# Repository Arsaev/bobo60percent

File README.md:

# bobo60percent
It is a custom mechanical keyboard that I working on.

Features
- clickable knob 
- small screen 
- HHKB like layout 
- rgb highlight and backlight
- USB-C

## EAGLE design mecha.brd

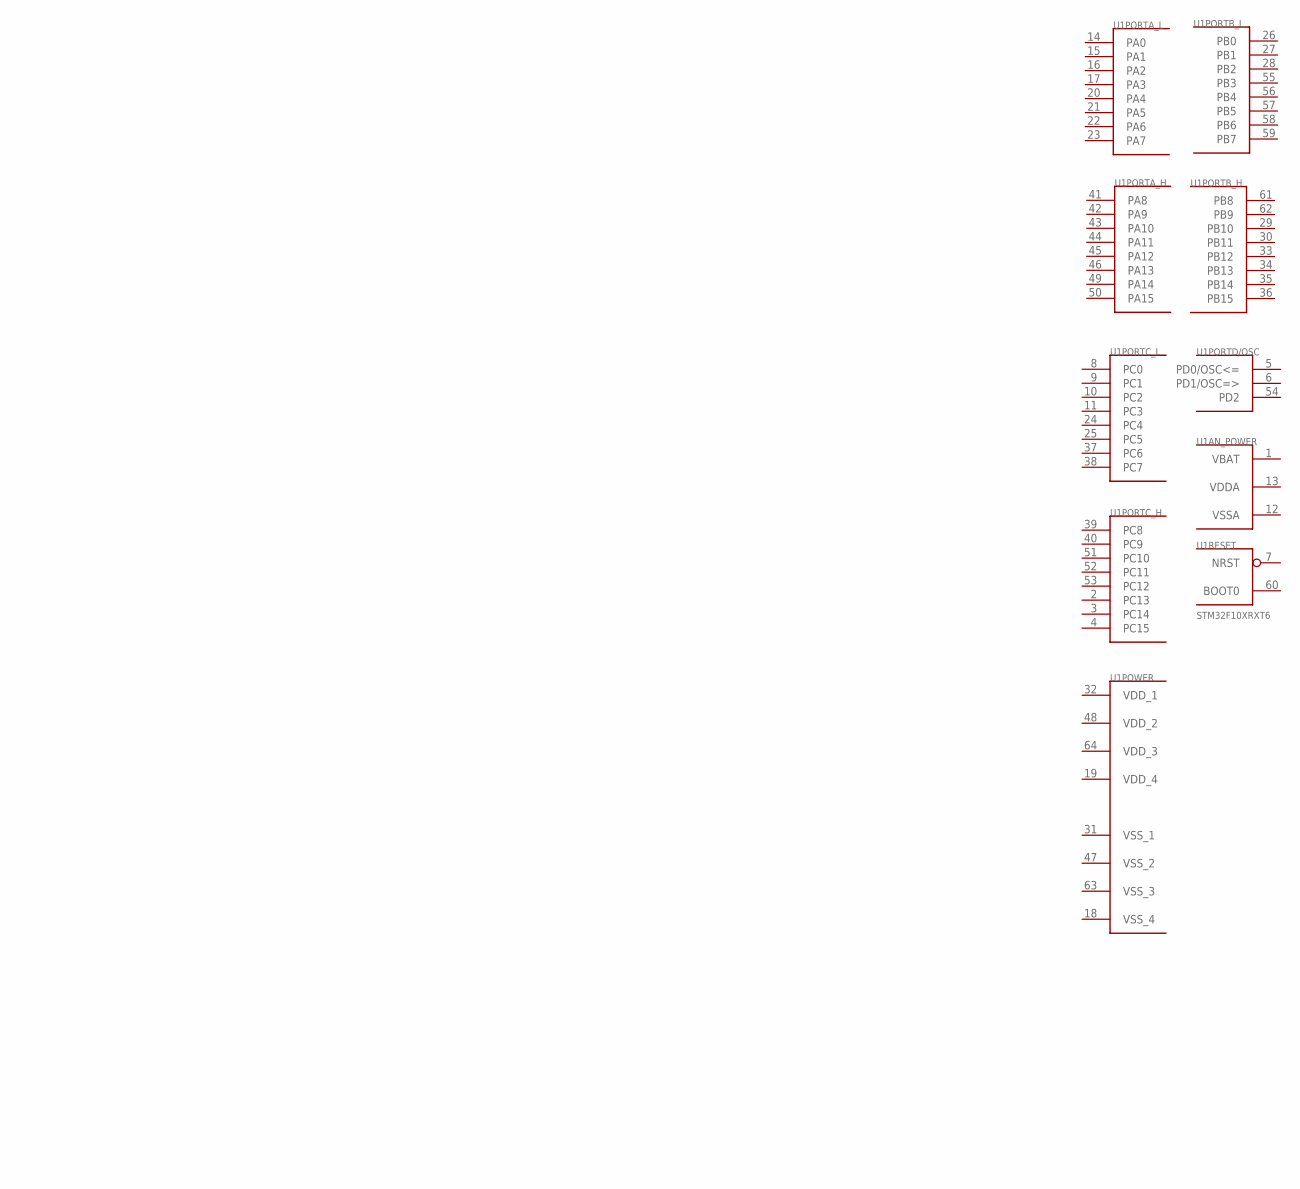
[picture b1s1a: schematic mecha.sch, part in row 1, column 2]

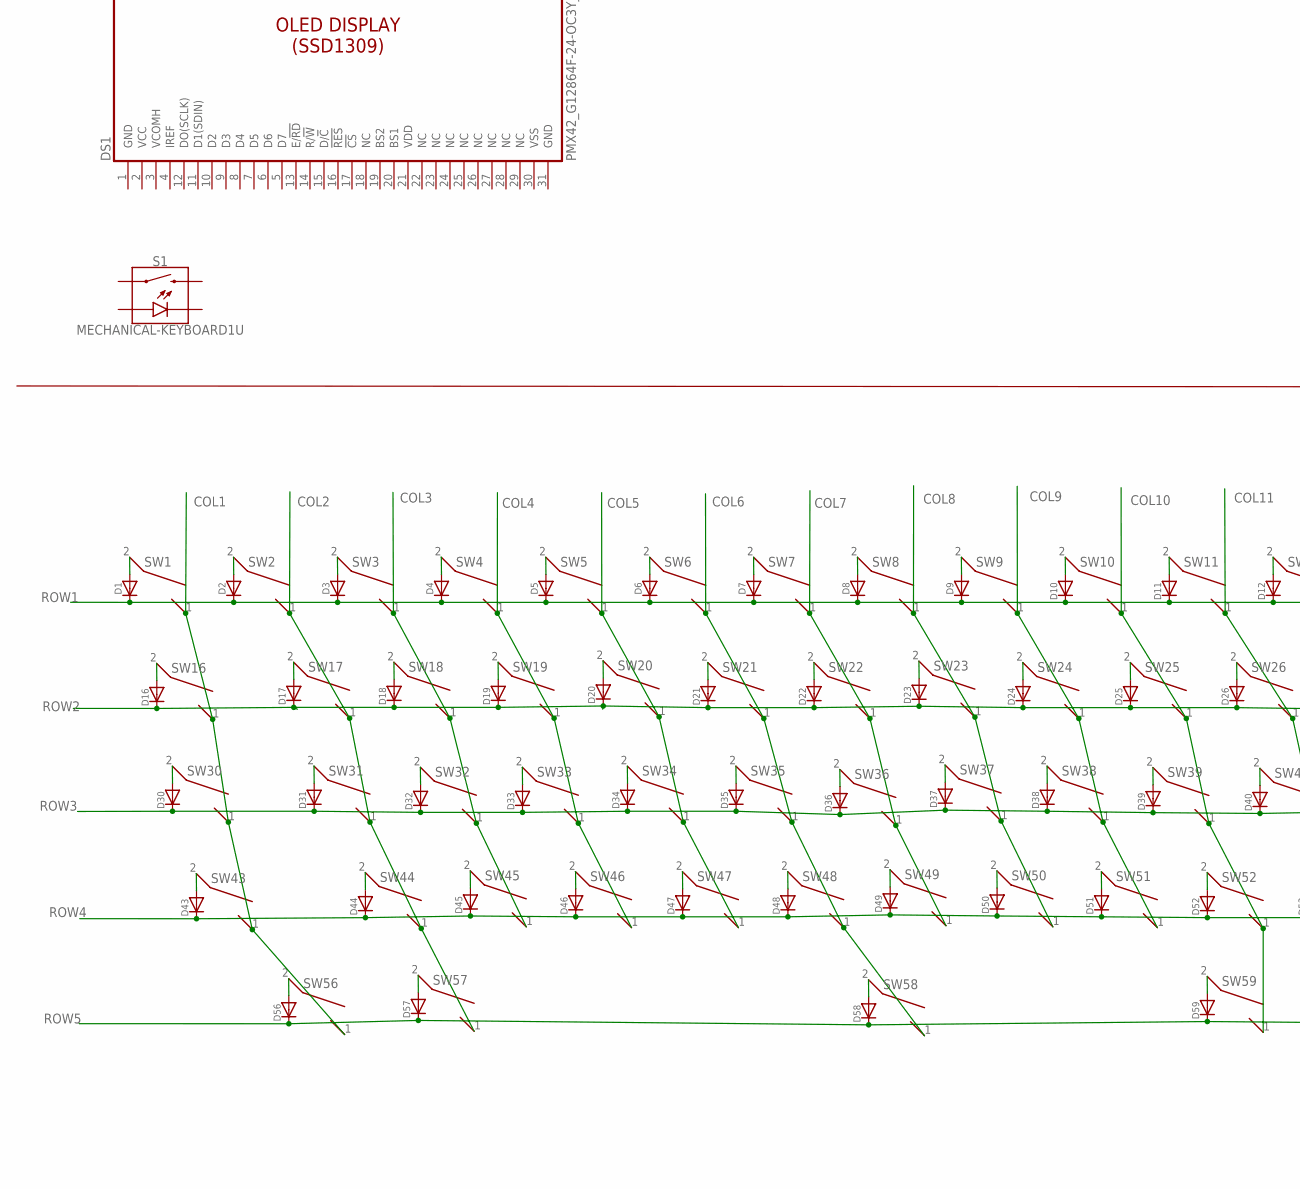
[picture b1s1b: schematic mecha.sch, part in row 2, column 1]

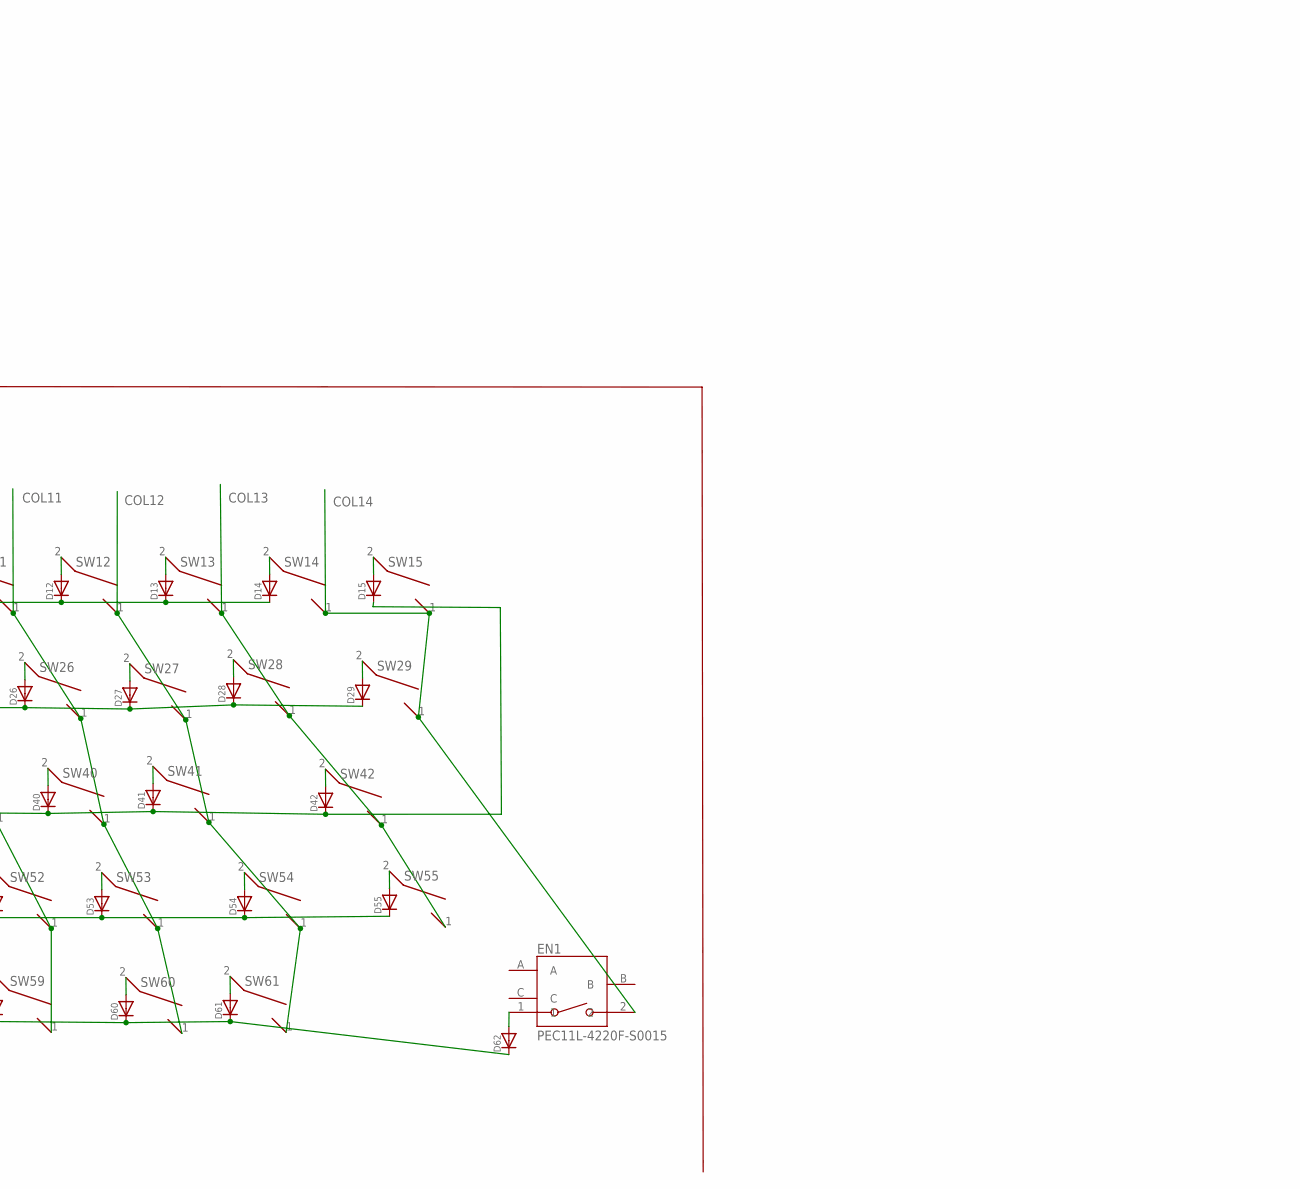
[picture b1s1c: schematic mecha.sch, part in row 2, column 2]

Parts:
D1, D2, D3, D4, D5, D6, D7, D8, D9, D10, D11, D12, D13, D14, D15, D16, D17, D18, D19, D20, D21, D22, D23, D24, D25, D26, D27, D28, D29, D30, D31, D32, D33, D34, D35, D36, D37, D38, D39, D40, D41, D42, D43, D44, D45, D46, D47, D48, D49, D50, D51, D52, D53, D54, D55, D56, D57, D58, D59, D60, D61, D62: DIODESOD-323F; SOD-323F
DS1: PMX42_G12864F-24-OC3Y_BOT
EN1: PEC11L-4220F-S0015
S1: MECHANICAL-KEYBOARD1U; CHERRY-MX-LED-1U
SW1, SW2, SW3, SW4, SW5, SW6, SW7, SW8, SW9, SW10, SW11, SW12, SW13, SW14, SW15, SW16, SW17, SW18, SW19, SW20, SW21, SW22, SW23, SW24, SW25, SW26, SW27, SW28, SW29, SW30, SW31, SW32, SW33, SW34, SW35, SW36, SW37, SW38, SW39, SW40, SW41, SW42, SW43, SW44, SW45, SW46, SW47, SW48, SW49, SW50, SW51, SW52, SW53, SW54, SW55, SW56, SW57, SW58, SW59, SW60, SW61: KAILH_SWITCH_SOCKET; SWITCH_SOCKET
U1: STM32F10XRXT6; TQFP64

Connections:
COL1: SW1.1 (2), SW16.1 (2), SW30.1 (2), SW43.1 (2), SW56.1 (2)
COL2: SW2.1 (2), SW17.1 (2), SW31.1 (2), SW44.1 (2), SW57.1 (2)
COL3: SW3.1 (2), SW18.1 (2), SW32.1 (2), SW45.1 (2)
COL4: SW4.1 (2), SW19.1 (2), SW33.1 (2), SW46.1 (2)
COL5: SW5.1 (2), SW20.1 (2), SW34.1 (2), SW47.1 (2)
COL6: SW6.1 (2), SW21.1 (2), SW35.1 (2), SW48.1 (2), SW58.1 (2)
COL7: SW7.1 (2), SW22.1 (2), SW36.1 (2), SW49.1 (2)
COL8: SW8.1 (2), SW23.1 (2), SW37.1 (2), SW50.1 (2)
COL9: SW9.1 (2), SW24.1 (2), SW38.1 (2), SW51.1 (2)
COL10: SW10.1 (2), SW25.1 (2), SW39.1 (2), SW52.1 (2), SW59.1 (2)
COL11: SW11.1 (2), SW26.1 (2), SW40.1 (2), SW53.1 (2), SW60.1 (2)
COL12: SW12.1 (2), SW27.1 (2), SW41.1 (2), SW54.1 (2), SW61.1 (2)
COL13: SW13.1 (2), SW28.1 (2), SW42.1 (2), SW55.1 (2)
COL14: EN1.2, SW14.1 (2), SW15.1 (2), SW29.1 (2)
GND: DS1.1 (GND), DS1.31 (GND)
unnamed: D1.A, SW1.2 (1)
unnamed: D2.A, SW2.2 (1)
unnamed: D3.A, SW3.2 (1)
unnamed: D4.A, SW4.2 (1)
unnamed: D5.A, SW5.2 (1)
unnamed: D6.A, SW6.2 (1)
unnamed: D7.A, SW7.2 (1)
unnamed: D8.A, SW8.2 (1)
unnamed: D9.A, SW9.2 (1)
unnamed: D10.A, SW10.2 (1)
unnamed: D11.A, SW11.2 (1)
unnamed: D12.A, SW12.2 (1)
unnamed: D13.A, SW13.2 (1)
unnamed: D14.A, SW14.2 (1)
unnamed: D15.A, SW15.2 (1)
unnamed: D16.A, SW16.2 (1)
unnamed: D17.A, SW17.2 (1)
unnamed: D18.A, SW18.2 (1)
unnamed: D19.A, SW19.2 (1)
unnamed: D20.A, SW20.2 (1)
unnamed: D21.A, SW21.2 (1)
unnamed: D22.A, SW22.2 (1)
unnamed: D23.A, SW23.2 (1)
unnamed: D24.A, SW24.2 (1)
unnamed: D25.A, SW25.2 (1)
unnamed: D26.A, SW26.2 (1)
unnamed: D27.A, SW27.2 (1)
unnamed: D28.A, SW28.2 (1)
unnamed: D29.A, SW29.2 (1)
unnamed: D30.A, SW30.2 (1)
unnamed: D31.A, SW31.2 (1)
unnamed: D32.A, SW32.2 (1)
unnamed: D33.A, SW33.2 (1)
unnamed: D34.A, SW34.2 (1)
unnamed: D35.A, SW35.2 (1)
unnamed: D36.A, SW36.2 (1)
unnamed: D37.A, SW37.2 (1)
unnamed: D38.A, SW38.2 (1)
unnamed: D39.A, SW39.2 (1)
unnamed: D40.A, SW40.2 (1)
unnamed: D41.A, SW41.2 (1)
unnamed: D42.A, SW42.2 (1)
unnamed: D43.A, SW43.2 (1)
unnamed: D44.A, SW44.2 (1)
unnamed: D45.A, SW45.2 (1)
unnamed: D46.A, SW46.2 (1)
unnamed: D47.A, SW47.2 (1)
unnamed: D48.A, SW48.2 (1)
unnamed: D49.A, SW49.2 (1)
unnamed: D50.A, SW50.2 (1)
unnamed: D51.A, SW51.2 (1)
unnamed: D52.A, SW52.2 (1)
unnamed: D53.A, SW53.2 (1)
unnamed: D54.A, SW54.2 (1)
unnamed: D55.A, SW55.2 (1)
unnamed: D56.A, SW56.2 (1)
unnamed: D57.A, SW57.2 (1)
unnamed: D58.A, SW58.2 (1)
unnamed: D59.A, SW59.2 (1)
unnamed: D60.A, SW60.2 (1)
unnamed: D61.A, SW61.2 (1)
unnamed: D62.A, EN1.1
ROW1: D1.C, D2.C, D3.C, D4.C, D5.C, D6.C, D7.C, D8.C, D9.C, D10.C, D11.C, D12.C, D13.C, D14.C
ROW2: D16.C, D17.C, D18.C, D19.C, D20.C, D21.C, D22.C, D23.C, D24.C, D25.C, D26.C, D27.C, D28.C, D29.C
ROW3: D15.C, D30.C, D31.C, D32.C, D33.C, D34.C, D35.C, D36.C, D37.C, D38.C, D39.C, D40.C, D41.C, D42.C
ROW4: D43.C, D44.C, D45.C, D46.C, D47.C, D48.C, D49.C, D50.C, D51.C, D52.C, D53.C, D54.C, D55.C
ROW5: D56.C, D57.C, D58.C, D59.C, D60.C, D61.C, D62.C
VBAT: U1.1 (VBAT)
VCC: DS1.2 (VCC)
VDD: DS1.21 (VDD)
VDDA: U1.13 (VDDA)
VDD_1: U1.32 (VDD_1)
VDD_2: U1.48 (VDD_2)
VDD_3: U1.64 (VDD_3)
VDD_4: U1.19 (VDD_4)
VSS: DS1.30 (VSS)
VSSA: U1.12 (VSSA)
VSS_1: U1.31 (VSS_1)
VSS_2: U1.47 (VSS_2)
VSS_3: U1.63 (VSS_3)
VSS_4: U1.18 (VSS_4)

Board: 2 copper layers, 127 parts (62 on the bottom side), 82 nets, no tracks yet.

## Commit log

2021-08-23 initial commit with keyboard matrix and hotswap sockets
2021-08-23 add keybaoard layout files for keyboard-layout-editor

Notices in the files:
parts and their libraries:
SparkFun-Switches: Licensing: Creative Commons ShareAlike 4.0 International - https://creativecommons.org/licenses/by-sa/4.0
